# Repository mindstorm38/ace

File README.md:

# ACE Concept
ACE ( Air Comprimé Explosif / Explosive Compressed Air ) resources

Ces canons utilisent un réservoir, ou un volume d'air suffisant pour propulser le projectile hors du canon est comprimé jusqu'à ce qu'une paroi située entre le réservoir et le canon relâche la pression d'un coup, libérant une énorme quantité d'énergie.

Notes à propos de ce système :
- Plus bruyant qu'un canon à air comprimé classique, mais tout de même moins qu'une arme à feu, ne nécessite donc pas de casque.
- Aucune fumée produite (si ce n'est de la vapeur de condensation)
- La puissance du projectile dépend de la pression de rupture de la paroi séparant le réservoir et le canon, du volume, du diamètre et de la longueur du canon
- Nécessite une arrivée d'air suffisante pour atteindre la pression de rupture de la paroi mais ne nécessite pas beaucoup de débit

Système inventé début 2017.

> Ce dépôt est public, cela à pour unique but de concevoir le système le plus fiable et efficace, mais en aucun je ne me tiendrais responsable de quelconque utilisation illégale de ce canon.

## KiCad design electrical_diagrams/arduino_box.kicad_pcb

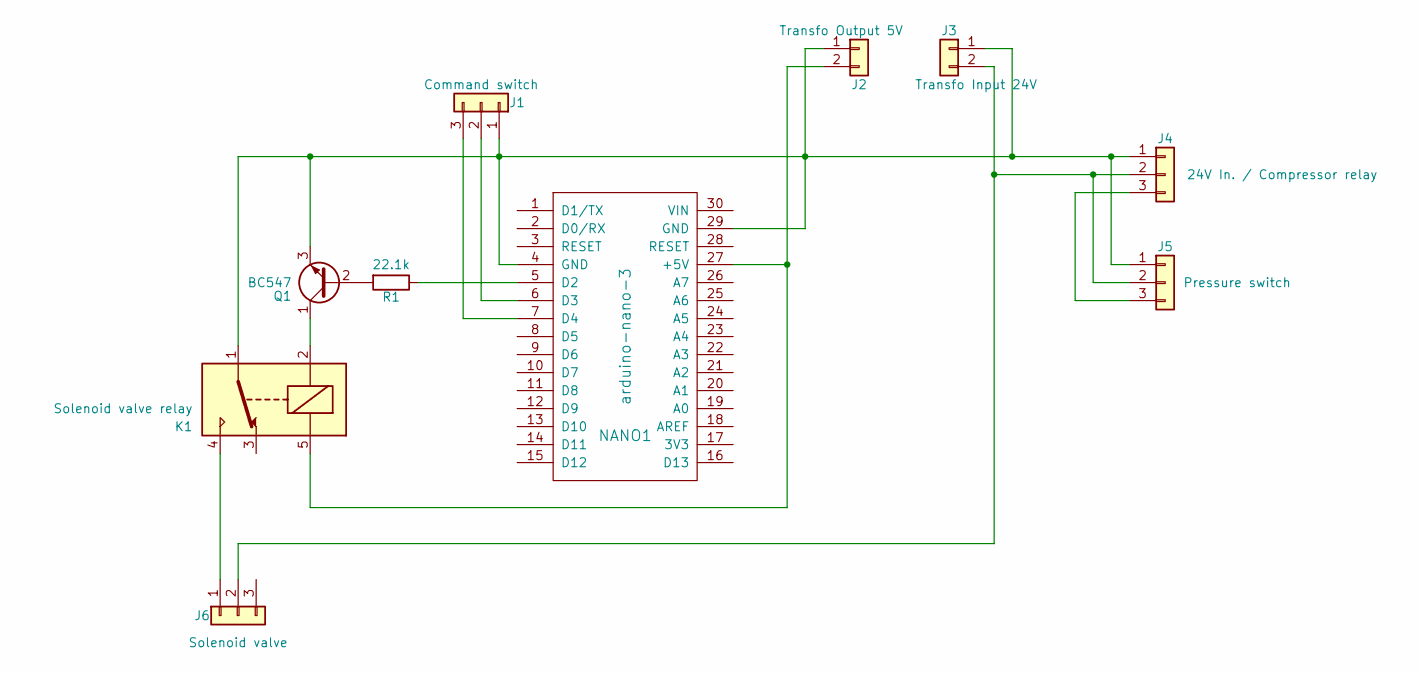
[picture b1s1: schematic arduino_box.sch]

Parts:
J1: Command switch; SL-103-X-XX_1x03
J2: Transfo Output 5V; SL-102-X-XX_1x02
J3: Transfo Input 24V; SL-102-X-XX_1x02
J4: 24V In. / Compressor relay; SL-103-X-XX_1x03
J5: Pressure switch; SL-103-X-XX_1x03
J6: Solenoid valve; SL-103-X-XX_1x03
K1: Solenoid valve relay; Relay_SPDT_SANYOU_SRD_Series_Form_C
NANO1: arduino-nano-3
Q1: BC547; OldSowjetaera_Transistor_Type-II_SmallPads
R1: 22.1k; R_Axial_DIN0204_L3.6mm_D1.6mm_P7.62mm_Horizontal

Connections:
unnamed: J1.1, J2.1, J3.1, J4.1, J5.1, K1.1, NANO1.4 (GND), NANO1.29 (GND), Q1.3 (E)
unnamed: J1.2, NANO1.6 (D3)
unnamed: J1.3, NANO1.7 (D4)
unnamed: J2.2, K1.5, NANO1.27 (+5V)
unnamed: J3.2, J4.2, J5.2, J6.2
unnamed: J4.3, J5.3
unnamed: J6.1, K1.4
unnamed: K1.2, Q1.1 (C)
unnamed: NANO1.5 (D2), R1.1
unnamed: Q1.2 (B), R1.2

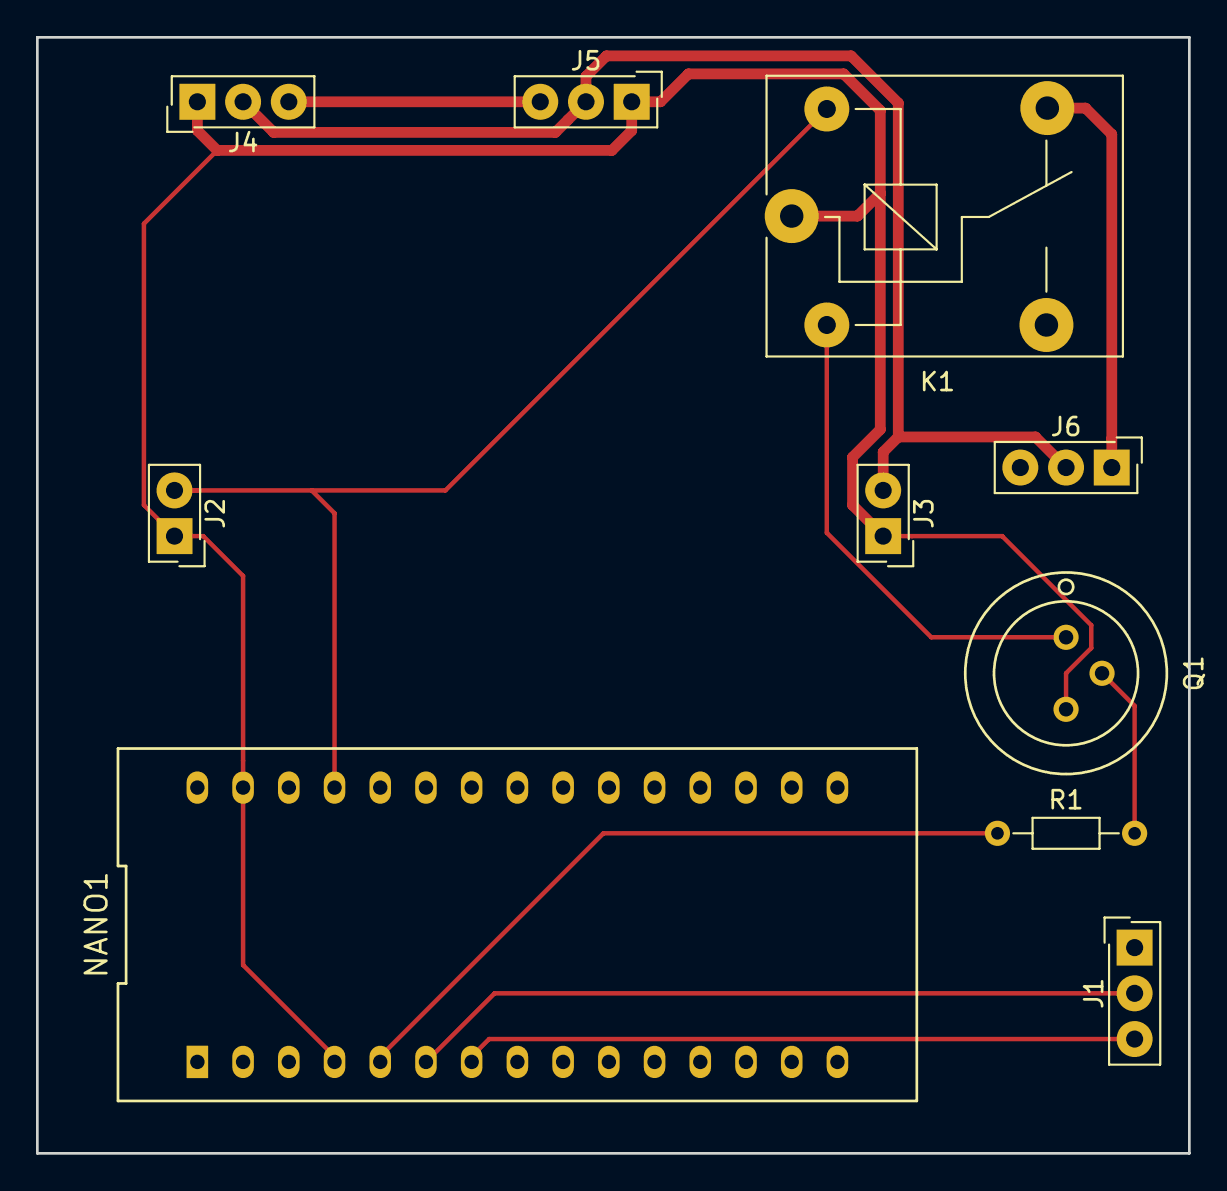
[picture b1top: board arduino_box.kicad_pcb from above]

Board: 2 copper layers, 64.0 x 62.0 mm, 10 parts (0 on the bottom side), 10 nets.

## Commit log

2018-05-24 Adding arduino code resources
2018-05-25 Adding Kicad project
2019-03-24 Added all inventor project.
2019-03-25 Added WIP ACE-FP 12
2019-03-26 Added one more prototype of ACE-FP 12, and changed READMEs
2019-03-26 Finished prototype 2, working on third...
2019-03-26 Added weight for ACE-FP 12 Prot 2
2019-03-26 Working on ACE-FP 12 Prototype 3 ...
2019-03-26 Changed weight in README
2019-03-26 Corrected READMEs
2019-03-29 Changed some size for better compression
2019-04-06 Working on ACE-FP 12 Prot 3
2019-04-07 Update drawing
2019-04-10 Working on Semi-Automatic prototype ..
2022-12-11 Fixed some typos in README
